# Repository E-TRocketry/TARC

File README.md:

# Space Pickles
## Official Electrical Repository of TARC team based in American High School
### This repository schematics, PCBs, and plans for the electrical systems of the 2024 Space Pickles Rocket

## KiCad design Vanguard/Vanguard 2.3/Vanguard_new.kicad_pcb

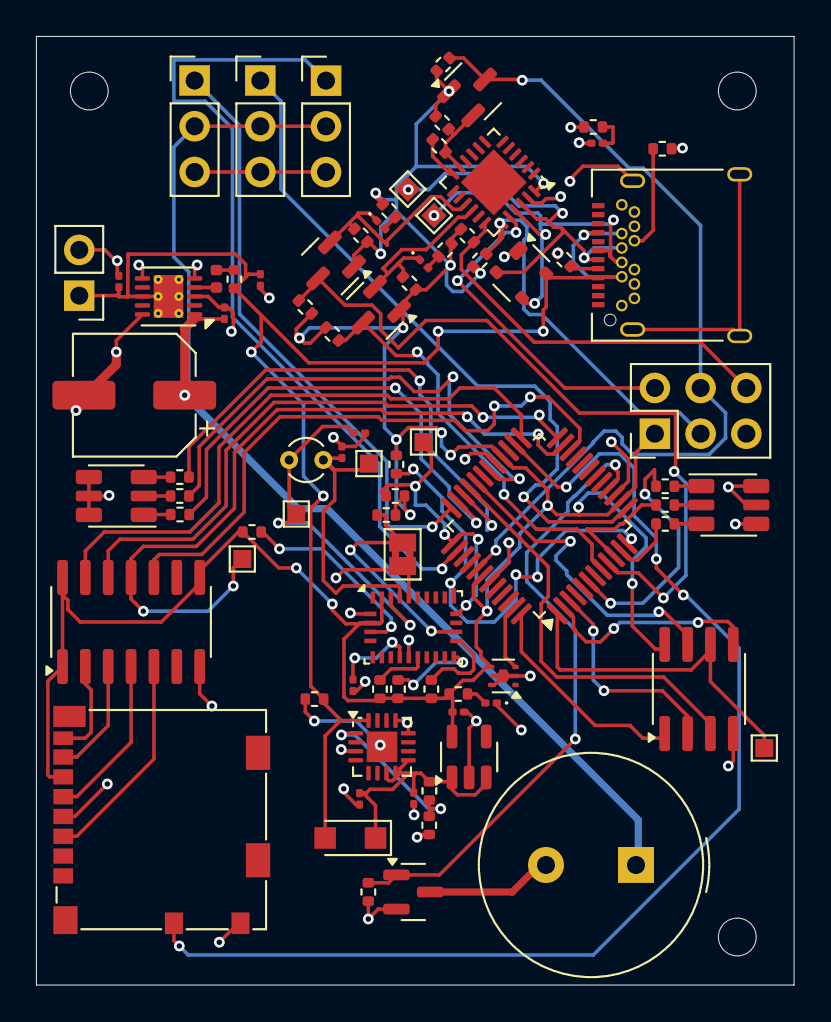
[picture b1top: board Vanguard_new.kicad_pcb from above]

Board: 4 copper layers, 42.1 x 52.7 mm, 82 parts (0 on the bottom side), 69 nets.

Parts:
ADR1: SolderJumper-2_P1.3mm_Bridged2Bar_Pad1.0x1.5mm
BZ1: Buzzer; Buzzer_TDK_PS1240P02BT_D12.2mm_H6.5mm
C1: 4n7; C_0201_0603Metric
C2, C3: 22p; C_0201_0603Metric
C4, C5: 22u; C_0201_0603Metric
C6, C11: 1u; C_0201_0603Metric
C7: 0u1; C_0201_0603Metric
C8: 10u; C_0201_0603Metric
C9: 2u2; C_0201_0603Metric
C10: 100u; CP_Elec_6.3x5.4
D1: PRTR5V0U2X; SOT-143
D2, D3: LED; LED_0201_0603Metric
D5: GREEN; LED_0201_0603Metric
D6: PMEG6020ER; Nexperia_CFP3_SOD-123W
J1: USB_C_Receptacle_USB2.0_16P; USB_C_Receptacle_Amphenol_12401548E4-2A
J2: Conn_02x03_Pin; PinHeader_2x03_P2.54mm_Vertical
J3: Micro_SD_Card_Det1; microSD_HC_Molex_104031-0811
J4: STARBOARD_SERVO; PinHeader_1x03_P2.54mm_Vertical
J5: PORTSIDE_SERVO; PinHeader_1x03_P2.54mm_Vertical
J6: Conn_01x02_Pin; PinHeader_1x02_P2.54mm_Vertical
J7: EJECTION_SERVO; PinHeader_1x03_P2.54mm_Vertical
L1: 6u8; L_0402_1005Metric
PORTSIDE_RGB1: SMLVN6RGB; LED_ROHM_SMLVN6
Q1, Q2, Q3, Q4: BSS138; SOT-23
R1: 1M; R_0402_1005Metric
R2, R6, R7, R9, R10, R11, R12, R13, R19, R20: 4k7; R_0402_1005Metric
R3, R4: 330; R_0402_1005Metric
R5: 0; R_0402_1005Metric
R14, R15: 100k; R_0402_1005Metric
R16: 19k1; R_0402_1005Metric
R17: 330R; R_0402_1005Metric
R18, R23, R24: 10k; R_0402_1005Metric
R21, R22, R34: 2k2; R_0402_1005Metric
R25, R26, R27, R28, R29, R30: 220; R_0402_1005Metric
R31, R32: 5k1; R_0402_1005Metric
R33: 5m; R_0402_1005Metric
STARBOARD_RGB1: SMLVN6RGB; LED_ROHM_SMLVN6
TP1, TP2, TP3, TP4, TP5, TP6, TP7: TestPoint; TestPoint_Pad_1.0x1.0mm
U1: ATSAMD11D14A-M; QFN-24-1EP_4x4mm_P0.5mm_EP2.6x2.6mm
U2: ATmega4809-A; TQFP-48_7x7mm_P0.5mm
U3: AT25DF641A-SH-T; SOIC-8_3.9x4.9mm_P1.27mm
U4: AP2112K-3.3; SOT-23-5
U5: BD1020HFV; HVSOF5
U6: BNO086; LGA-28_5.2x3.8mm_P0.5mm
U7: TXB0104D; SOIC-14_3.9x8.7mm_P1.27mm
U8: TPS61092; DFN-10-1EP_3x3mm_P0.5mm_EP1.65x2.38mm_ThermalVias
U9: MPM3610AGQV-P; QFN-16-1EP_3x3mm_P0.5mm_EP1.7x1.7mm
Y1: 32.768kHz; Crystal_C26-LF_D2.1mm_L6.5mm_Vertical

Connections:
+3.3V: C6.1, J2.1, J3.6 (VSS), Q1.1 (G), Q2.1 (G), Q3.1 (G), R2.1, R3.1, R4.1, R6.1, R7.1, R9.1, R10.1, R11.1, R12.1, R13.1, R17.1, R18.2, R19.2, R20.2, R21.1, R22.1, R23.1, R24.1, U1.24 (VDD), U2.14 (VCC), U2.28 (AVCC), U2.42 (VCC), U3.8 (VCC), U4.5 (VOUT), U5.4 (VDD), U6.3 (VDD), U6.28 (VDDIO), U7.1 (VCCA), U7.8 (OE), U7.14 (VCCB)
+5V: BZ1.1 (+), C9.1, C10.1, J4.2, J5.2, J7.2, U8.1 (VOUT)
/RX_UPDI: R5.1, U1.12 (PA15)
/TX_UPDI: Q1.2 (S), R5.2, R6.2, U1.11 (PA14)
BUZZER: Q4.1 (G), R34.1, U2.16 (PC4)
CD: J3.9 (DET), U2.26 (PD6)
D4: TP3.1, U2.23 (PD3), U7.11 (B3)
D5: U2.22 (PD2), U7.10 (B4)
D6: U2.24 (PD4), U7.12 (B2)
D7: U2.25 (PD5), U7.13 (B1)
EJEC_SERVO: J7.1, U2.38 (PF4)
GND: ADR1.1 (A), C1.1, C1.2, C2.2, C3.2, C4.2, C5.2, C6.2, C7.2, C8.2, C9.2, C10.2, C11.2, D1.1 (GND), D5.1 (K), J1.A1 (GND), J1.A12 (GND), J1.B1 (GND), J1.B12 (GND), J1.S1 (SHIELD), J2.5, J3.4 (VDD), J3.10 (SHIELD), J4.3, J5.3, J6.2, J7.3, PORTSIDE_RGB1.4 (GK), PORTSIDE_RGB1.5 (RK), PORTSIDE_RGB1.6 (BK), Q4.2 (S), R1.1, R1.2, R16.2, R31.2, R32.2, R34.2, STARBOARD_RGB1.4 (GK), STARBOARD_RGB1.5 (RK), STARBOARD_RGB1.6 (BK), U1.23 (GND), U2.15 (GND), U2.29 (GND), U2.43 (GND), U3.4 (GND), U4.2 (GND), U5.2 (PG), U5.5 (GND), U6.2 (GND), U6.10 (CLKSEL0), U6.25 (GNDIO), U7.7 (GND), U8.3 (SW), U8.5 (PGND), U8.6 (PGND), U8.7 (PGND), U8.10 (SYNC), U9.3 (AGND), U9.12 (PGND), U9.13 (PGND), U9.14 (PGND)
HOLD: U2.32 (PE2), U3.7 (~HOLD)
unnamed: ADR1.2 (B), R23.2, U6.17 (SA0/H_MOSI)
unnamed: BZ1.2 (-), Q4.3 (D)
unnamed: D1.2 (I/O1), J1.A6 (D+), J1.B6 (D+), TP1.1, U1.22 (PA25)
unnamed: D1.3 (I/O2), J1.A7 (D-), J1.B7 (D-), TP2.1, U1.21 (PA24)
unnamed: D2.2 (A), R4.2
unnamed: D2.1 (K), Q3.2 (S), R9.2, U1.15 (PA22)
unnamed: D3.2 (A), R3.2
unnamed: D3.1 (K), Q2.2 (S), R10.2, U1.16 (PA23)
unnamed: D5.2 (A), R17.2
unnamed: C5.1, C11.1, D6.1 (K), R15.1, U4.1 (VIN), U4.3 (EN), U9.7 (OUT), U9.8 (OUT), U9.9 (OUT)
unnamed: J1.A5 (CC1), R31.1
unnamed: J1.B5 (CC2), R32.1
unnamed: J2.2, U1.20 (PA31/SWDIO)
unnamed: J2.3, R2.2, U1.19 (PA30/SWCLK)
unnamed: J2.6, R11.2, U1.18 (PA28/~RST)
unnamed: J3.5 (CLK), U7.4 (A3)
unnamed: J3.3 (CMD), U7.5 (A4)
unnamed: J3.7 (DAT0), U7.3 (A2)
unnamed: J3.8 (DAT1), U7.2 (A1)
unnamed: L1.1, R33.1
unnamed: L1.2, U8.4 (SW)
unnamed: PORTSIDE_RGB1.1 (BA), R28.1
unnamed: PORTSIDE_RGB1.3 (GA), R30.1
unnamed: PORTSIDE_RGB1.2 (RA), R29.1
unnamed: R25.2, STARBOARD_RGB1.1 (BA)
unnamed: R27.2, STARBOARD_RGB1.3 (GA)
unnamed: R26.2, STARBOARD_RGB1.2 (RA)
unnamed: C7.1, U6.9 (CAP)
unnamed: R19.1, U6.15 (ENV_SCL)
unnamed: R20.1, U6.16 (ENV_SDA)
unnamed: C3.1, TP5.1, U6.27 (XIN32), Y1.2
unnamed: C2.1, TP6.1, U6.26 (XOUT32/CLKSEL1), Y1.1
unnamed: R24.2, U6.4 (~BOOT)
unnamed: R18.1, U6.11 (~RST)
unnamed: R14.2, U9.17 (EN)
unnamed: R15.2, R16.1, U9.1 (FB)
PA0/MISO: U2.3 (PA7), U3.2 (SO(SOI))
PA1/MOSI: U2.2 (PA6), U3.5 (SI(SIO))
PA2/SCK: TP4.1, U2.1 (PA5), U3.6 (SCK)
PA3/SS: U2.48 (PA4), U3.1 (~CS)
PORT_BLUE: R28.2, U2.35 (PF1)
PORT_GREEN: R30.2, U2.34 (PF0)
PORT_RED: R29.2, U2.30 (PE0)
PORT_SERVO: J5.1, U2.13 (PC3)
POWER_STAB: C4.1, C8.1, D1.4 (VCC), D6.2 (A), J1.A4 (VBUS), J1.A9 (VBUS), J1.B4 (VBUS), J1.B9 (VBUS), J6.1, R14.1, R33.2, U8.8 (VBAT), U8.11 (EN), U9.16 (IN)
RX0: Q3.3 (D), R12.2, U2.9 (PB5)
SCL: R22.2, TP7.1, U2.37 (PF3), U6.19 (H_SCL/SCK/RX)
SDA: R21.2, U2.12 (PC2), U6.20 (H_SDA/H_MISO/TX)
STAR_BLUE: R25.1, U2.6 (PB2)
STAR_GREEN: R27.1, U2.11 (PC1)
STAR_RED: R26.1, U2.10 (PC0)
STAR_SERVO: J4.1, U2.36 (PF2)
TEMP_SENSOR: U2.47 (PA3), U5.3 (OUT)
TX0: Q2.3 (D), R13.2, U2.8 (PB4)
UPDI: J2.4, Q1.3 (D), R7.2, U2.41 (UPDI)
WP: U2.33 (PE3), U3.3 (~WP)

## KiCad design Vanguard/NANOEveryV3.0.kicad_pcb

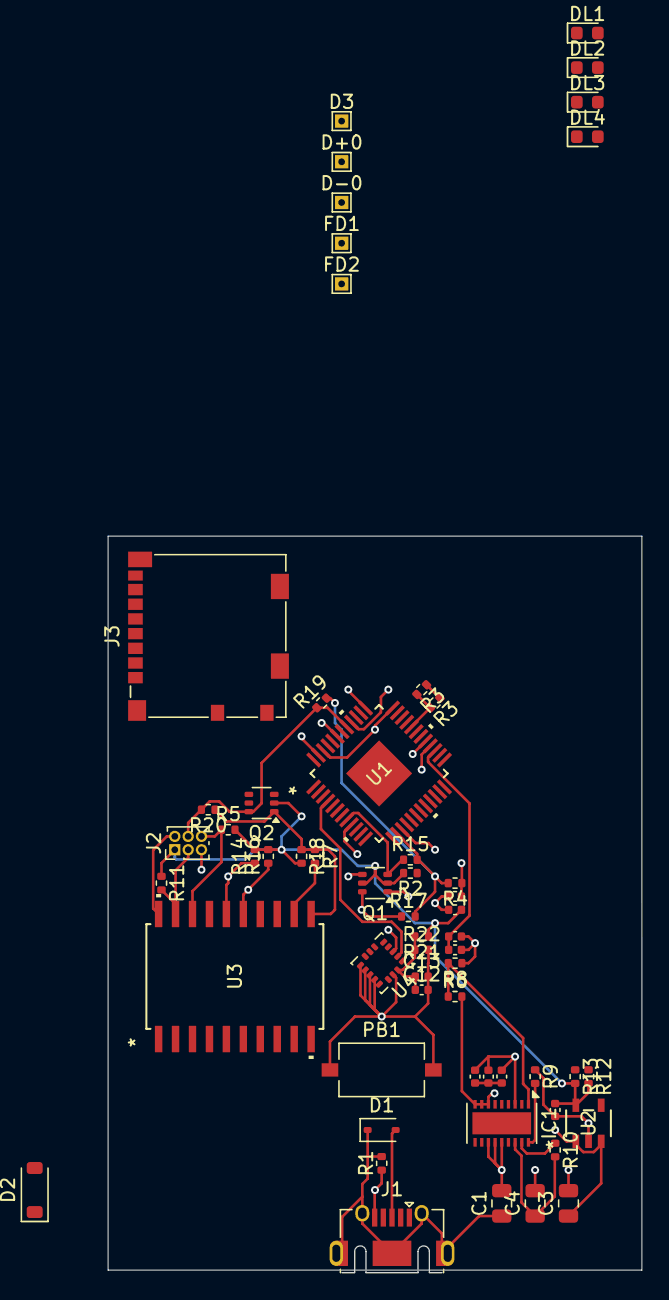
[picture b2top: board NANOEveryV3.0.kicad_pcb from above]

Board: 6 copper layers, 40.0 x 55.0 mm, 58 parts (0 on the bottom side), 29 nets.

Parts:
C1: 4n7; C_0805_2012Metric
C2, C7, C8, C10, C11: 100n; C_0402_1005Metric
C3, C4: 22u; C_0805_2012Metric
C5, C9, C12: 4u7; C_0402_1005Metric
C6: 1u; C_0402_1005Metric
C13: 0u1; C_0402_1005Metric
D1: PRTR5V; D_SOD-323
D2: PMEG6020; D_SOD-123
D3: DNP; TestPoint_THTPad_1.0x1.0mm_Drill0.5mm
D+0: DNP; TestPoint_THTPad_1.0x1.0mm_Drill0.5mm
D-0: DNP; TestPoint_THTPad_1.0x1.0mm_Drill0.5mm
DL1, DL3, DL4: YELLOW; LED_0603_1608Metric
DL2: GREEN; LED_0603_1608Metric
FD1, FD2: DNP; TestPoint_THTPad_1.0x1.0mm_Drill0.5mm
IC1: MPM3610; DFN-18-1EP_3x5mm_P0.5mm_EP1.66x4.4mm
J1: -; USB_Micro-AB_Molex_47590-0001
J2: DNP; PinHeader_2x03_P1.00mm_Vertical
J3: Micro_SD_Card_Det1; microSD_HC_Molex_104031-0811
PB1: PTS820; SW_Tactile_SPST_NO_Straight_CK_PTS636Sx25SMTRLFS
Q1, Q2: BSS138PS; SOT-363_SC-70-6
R1: 1M; R_0402_1005Metric
R2, R3, R3#2, R12, R13: 330R; R_0402_1005Metric
R4, R6, R10: 100k; R_0402_1005Metric
R5, R11, R14, R15, R16, R17, R18, R19: 4k7; R_0402_1005Metric
R7: 0R; R_0402_1005Metric
R8: 19k1; R_0402_1005Metric
R9: 39k; R_0402_1005Metric
R20: DNP; R_0402_1005Metric
R21: 538Ω; R_0402_1005Metric
R22: 645Ω; R_0402_1005Metric
U1: ATMEGA4809; TQFP48_7x7MC_MCH
U2: AP2112K-3.3; SOT_RG1_DIO
U3: ATSAMD11D14A; SOIC20_12P8X7P5_MCH
U4: ICM-20602; LGA-16_3x3mm_P0.5mm_LayoutBorder3x5y

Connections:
1.8v temp sda: U1.36 (PF02), U1.46 (PA02), U4.3 (SDA/SDI)
+3V3: C6.1, C11.2, J2.1, Q1.2 (G), Q1.5 (G), Q2.2 (G), R2.2, R5.2, R11.1, R12.2, R13.2, R14.2, R16.2, R18.2, R21.1, U2.5 (OUT)
+5V: C8.2, C9.2, C10.2, R4.2, R15.2, R17.2, R19.2, U1.14 (VDD@2), U1.28 (AVDD), U1.42 (VDD@1)
/A5/SCL: U1.37 (PF03), U1.47 (PA03)
/AREF: C5.1, C7.1, U1.27 (PD07)
/D9~: U1.4 (PB00), U4.2 (SCL/SPC)
/RESETN: C2.1, R4.1, U1.40 (RST/PF06)
/RX0: J3.5 (CLK), Q1.6 (D), R17.1, U1.9 (PB05)
/RX_D11: Q1.4 (S), R14.1, U3.16 (PA23)
/RX_UPDI: R7.2, U3.12 (PA15)
/SCK: R3.2, R3#2.2, U1.32 (PE02)
/TX0: Q1.3 (D), R15.1, U1.8 (PB04)
/TX_D11: Q1.1 (S), R16.1, U3.15 (PA22)
/TX_UPDI: Q2.1 (S), R7.1, R18.1, R20.1, U3.11 (PA14)
/UPDI: J2.4, Q2.6 (D), R19.1, R20.2, U1.41 (UPDI)
/USB_P: D1.2, J1.3
GND: C1.2, C2.2, C3.2, C4.2, C5.2, C6.2, C7.2, C8.1, C9.1, C10.1, C11.1, C12.2, C13.2, IC1.3 (AGND), IC1.12 (GND), IC1.13 (GND), IC1.14 (GND), J1.5, J2.5, J3.6 (VSS), PB1.1 (3), PB1.2 (3), R1.1, R8.1, R9.1, R22.2, U1.15 (GND@3), U1.29 (GND@2), U1.43 (GND@1), U2.2 (GND/ADJ), U4.9 (GND), U4.10 (GND), U4.11 (GND), U4.12 (GND), U4.13 (GND), U4.15 (GND)
unnamed: C1.1, D1.1, J1.6 (SH), R1.2
unnamed: R3.1, R3#2.1
unnamed: IC1.18 (AAM), R9.2
unnamed: IC1.17 (EN), R10.1
unnamed: IC1.1 (FB), R6.1, R8.2
unnamed: IC1.4 (SW), IC1.5 (SW), IC1.6 (SW), IC1.19 (SW)
unnamed: C4.1, IC1.16 (VIN), R10.2
unnamed: C3.1, IC1.7 (OUT), IC1.8 (OUT), IC1.9 (OUT), R6.2, U2.1 (IN), U2.3 (EN)
unnamed: J2.6, R5.1, U3.18 (PA28/RESETN)
unnamed: J2.3, R11.2, U3.19 (PA30/SWCLK)
unnamed: J2.2, U3.20 (PA31/SWDIO)
unnamed: C12.1, C13.1, R21.2, R22.1, U4.16 (VDD)

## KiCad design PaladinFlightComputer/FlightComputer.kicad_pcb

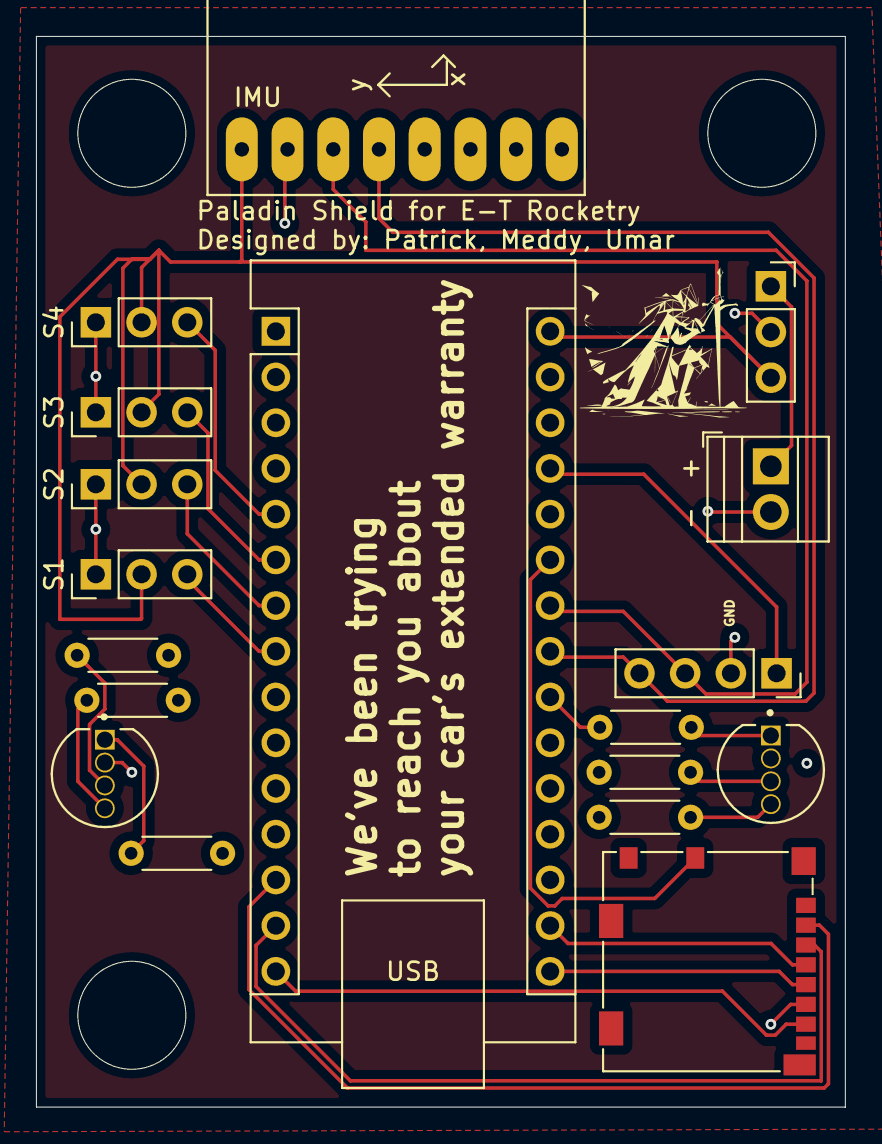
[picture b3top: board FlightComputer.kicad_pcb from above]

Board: 4 copper layers, 44.9 x 59.5 mm, 18 parts (0 on the bottom side), 28 nets.

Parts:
-  +: Screw_Terminal_01x02; TerminalBlock_Xinya_XY308-2.54-2P_1x02_P2.54mm_Horizontal
A1: Arduino_Nano_Every; Arduino_Nano
D2, D5: WP154A4SUREQBFZGC; LED_WP154A4SUREQBFZGC
J1: Micro_SD_Card_Det1; microSD_HC_Molex_104031-0811
J7: Conn_01x03; PinSocket_1x03_P2.54mm_Vertical
J8: Conn_01x04; PinSocket_1x04_P2.54mm_Vertical
R1, R2, R3, R4, R5, R6: R; R_Axial_DIN0204_L3.6mm_D1.6mm_P5.08mm_Horizontal
S1, S2, S3, S4: Conn_01x03; PinHeader_1x03_P2.54mm_Vertical
U1: GY-521

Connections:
GND: - +.2, A1.4 (GND), A1.29 (GND), D2.2, D5.2, J1.6 (VSS), J7.2, J8.2, S1.1, S2.1, S3.1, S4.1, U1.GND
unnamed: A1.17 (3V3), J1.4 (VDD)
unnamed: A1.27 (+5V), J8.1
unnamed: A1.20 (A1), R6.1
unnamed: A1.21 (A2), R5.1
unnamed: A1.22 (A3), R4.1
unnamed: A1.25 (A6), J1.9 (DET)
unnamed: A1.5 (D2), S4.3
unnamed: A1.6 (D3), S3.3
unnamed: A1.7 (D4), S2.3
unnamed: A1.8 (D5), S1.3
unnamed: A1.9 (D6), R1.1
unnamed: A1.10 (D7), R2.1
unnamed: A1.11 (D8), R3.1
unnamed: A1.13 (D10), J1.2 (DAT3/CD)
unnamed: A1.15 (MISO), J1.7 (DAT0)
unnamed: A1.14 (MOSI), J1.3 (CMD)
unnamed: A1.16 (SCK), J1.5 (CLK)
unnamed: A1.24 (SCL/A5), J8.3, U1.SCL
unnamed: A1.23 (SDA/A4), J8.4, U1.SDA
unnamed: A1.30 (VIN), J7.3, S1.2, S2.2, S3.2, S4.2, U1.VCC
unnamed: D2.1, R4.2
unnamed: D2.3, R5.2
unnamed: D2.4, R6.2
unnamed: D5.1, R3.2
unnamed: D5.3, R2.2
unnamed: D5.4, R1.2
unnamed: - +.1, J7.1

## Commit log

2024-08-09 Added STL FIle for Airbrake
2024-08-09 Gimablized Airbrake + Requirements
2024-08-09 Removed STL Files
2024-08-10 Added Airbrake STL
2024-08-10 Added TARC Materials
2024-08-10 sensor reading of barometer and imu
2024-08-10 Decrease Hz for sensor fusion
2024-08-21 intergrated sensor reading and zeroing
2024-10-07 added platform ino integration
2024-10-07 basic sim with interpolating tables
2024-10-08 Files via upload
2024-10-08 Paladin Test Push
2024-10-09 test push
2024-10-09 Initial File Upload
2024-10-09 Cleaning up non needed files
2024-10-10 Clean up unused files
2024-10-10 dual rgb lights on both sides
2024-10-11 Fottprint change
2024-10-11 Assign footprints for all caps
2024-10-12 components put into folders for public
2024-10-12 Till the LED part
    finishing it by 10 AM
2024-10-12 icm - 20606
2024-10-12 footprints for testpoints only
2024-10-12 (almost done) with the footprints
2024-10-13 Assigned footprints for mpm3610
2024-10-13 Removed connections from icm20602
2024-10-13 Added a Note for icm-20602
2024-10-14 sripathy wants to learn git
2024-10-14 sripathy changed his sexuality
2024-10-14 testing github bot
2024-10-14 reverting testing github bot changes
2024-10-15 micro_SD_card and footprints
2024-10-15 Start of layout
2024-10-15 wired lcm - no resistor values(umar)
2024-10-15 added resistor value
2024-10-16 added 2 temp sensors
    1 5v
    1 1.8v
    umar pls check the resistor values
    patrik please delete one whichever you want
2024-10-16 removed 5v and using 1.8v
2024-10-16 fixing small connection mistake
2024-10-17 some more layout shenangins
2024-10-17 assigned remaining footprint, added a high pass and a low pass filter capacitor to an analog sensor, removed connections from the i/o pins and connected it to the microcontroller
2024-10-17 Revert "assigned remaining footprint, added a high pass and a low pass filter capacitor to an analog sensor, removed connections from the i/o pins and connected it to the microcontroller"
    This reverts commit 5228414a55385d8cdf5987d2b94820cec65f7858.
2024-10-17 Reapply "assigned remaining footprint, added a high pass and a low pass filter capacitor to an analog sensor, removed connections from the i/o pins and connected it to the microcontroller"
    This reverts commit 22f8094e4c09e320e26257a78ee3dbc2d0131e87.
2024-10-17 Revert "Reapply "assigned remaining footprint, added a high pass and a low pass filter capacitor to an analog sensor, removed connections from the i/o pins and connected it to the microcontroller""
    This reverts commit f4597242ca1405cc35f70d25be6bb41070a348c1.
2024-10-17 removed i/o connections and sd card
2024-10-17 tiny analog change
2024-10-17 Added 2 decoupling capacitors to the temp. sensor
2024-10-17 slight changes in the capacitor arrangement
2024-10-18 finished layout except sd card
    lots of discontinuities need to be fixed
2024-10-18 added 2 footprints
2024-10-18 removed headers + added mcu
2024-10-18 New atmega chip added basic rewiring
2024-10-18 corrected parts
2024-10-18 ATSAMD11D14A changed
2024-10-19 opened a schematic
2024-10-19 changed file name
2024-10-19 testing---
2024-10-19 Welcome to V2 of vanguard (**not an error messsage**)
2024-10-19 opened a new schematic
2024-10-19 opened the USB input section
2024-10-20 moved files around
    sanctioned by patrick
2024-10-20 changes in the file exploror
2024-10-20 small schematic update
2024-10-20 square
2024-10-21 moved a uC inside the schematic
2024-10-21 small changes
2024-10-21 added flash card to schematic
2024-10-21 update removal
2024-10-21 Update README.md for electrical niche
2024-10-21 new mcu
2024-10-22 Input usb finished
2024-10-22 power stabilization done.
2024-10-22 noticed old mcu not deleted
2024-10-22 +temp +9axis
2024-10-23 finished bno086
    based off of https://docs.sparkfun.com/SparkFun_VR_IMU_Breakout_BNO086_QWIIC/assets/board_files/SparkFun_VR_IMU_Breakout_BNO086_QWIIC_Schematic_v10.pdf
2024-10-23 sd card done
2024-10-23 added, flash mem
    IMA KMS
2024-10-23 pin fix
2024-10-23 start of pcb layout
2024-10-23 idk summary
2024-10-23 starting work on pcb, imported parts
2024-10-23 finished footprints + moved to pcb
2024-10-24 schematic with leds and servos
2024-10-24 ref prev.
2024-10-24 buzzer added
2024-10-24 buzzer redone
2024-10-24 moved and wired 1 part
2024-10-24 symbol adressing, and pcb layout
2024-10-24 pcb work
2024-10-25 just in case push
2024-10-25 power stabilization done
2024-10-25 usb input almost done
2024-10-25 pcb laying out
2024-10-25 finished pcb wiring
2024-10-25 few silkscreen
2024-10-25 remove labels
2024-10-25 add 2 labels
2024-10-25 fixed sca pin and cleared some track-via clearnace issues
2024-10-26 schematic fixes
2024-10-26 fixed many errors
2024-10-26 file organization
2024-10-26 Added testpoints
2024-10-26 slight changes in the original sch. and added a testpoint
2024-10-27 REPLACEDthe USB_ and added new connections
2024-10-27 dev_file_changes( same as the v2 one)
2024-10-27 Added ref. sch
2024-10-27 Added tespoints
2024-10-27 Revert "Added testpoints"
    This reverts commit b260b8998230daf1f71bd3849bf22839f1098abd.
2024-10-27 Added_testpoints
2024-10-28 started pcb
2024-10-28 schematic + pcb changes
2024-10-29 pcb finished
2024-10-29 pcb changes
2024-10-30 made changes in the names of the resistor and caps, made changes in the usb c wiring, added a temperature sensor and added a label to the microcontroller
2024-10-31 Assigned footprints, added dnps and changed some connections in tx0 and rx0 pins
2024-11-01 Ran ERC and Assigned VBUS label
2024-11-01 Debugged some errors
2024-11-02 port side starboard servo port swap
2024-11-03 Small erc changes as the pcb guys recommeded
    @pchou05 @stygmatic what do you say? I am done with the sch but we still have some silly violations
2024-11-03 started wiring pcb
2024-11-04 finished wiring, no drc
2024-11-04 forgot a wire
2024-11-04 more wiring
2024-11-05 some drc fixes not done
2024-11-05 Vangaurd 2.2. Done.
2024-11-05 ejec servo added
2024-11-05 sd card rotato potato
2024-11-05 wire straight
2024-11-06 moved logo slightly and made more space
2024-11-06 vias
2024-11-07 Created production files
2024-11-07 Created production files in production folder but failed to generate BOM
2024-11-07 implamented changes from embedded engineers
2024-11-07 ground tracing improved
2024-11-07 fixed fill
2024-11-07 fixed copper pour
2024-11-07 9 axis imu 2.3
2024-11-08 not done 2.3 pcb
2024-11-08 added_one_plugin
2024-11-08 BOM_output
2024-11-08 nothing
2024-11-08 production???
2024-11-08 finished production files
2024-11-08 not done bom parts
2024-11-09 CSV update
2024-11-09 rev prev.
2024-11-15 changes in labels, capacitors and buzzer-mosfet
2024-11-16 added a 1uf cap to u4 input
2024-11-16 moved label "EJEC_SERVO" FROM pf3 to pf4 in MC and moved "scl" LABEL from PB0 TO pf3 and added a dnp in PB0
2024-11-16 saved the sch
2024-11-16 Closed KiCad
2024-11-20 an input label to U9 and MC label moved a bit
    Added a label in the input pin from U9 from the VBUS of USB. Moved the SPI pins and temperature sensor pins in the MC. @stygmatic have a look and ask me questions if needed
2024-11-20 Added a resistor in series with inductor(see servo power section)
2024-11-20 Removed dnps from 15 and 16 in the servo power and connected it to VOUT pin
2024-11-20 another tespoint
2024-11-21 Added a WP and HOLD labels in the Flash chip
2024-11-21 changed power labels
2024-11-21 KiCad closed
2024-11-22 added and removed a zener diode
2024-11-22 Assigned footprints testpoint, capacitors, resistors
2024-11-24 Changed the Vbus connection to sheild
2024-11-26 transfer to v2.3
2024-11-27 kicad
2024-11-27 pcb wiring
2024-11-27 layer fixes (kicad open)
2024-11-27 not done wiring
2024-11-27 pcb not done
2024-11-27 done pcb
2024-12-03 Centerd IMU
2024-12-06 diode added on vbus of usb c
    prevents back driving device on usbc line. Led added for power on indication.
2024-12-10 Production Files
